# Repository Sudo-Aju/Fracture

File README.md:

<div align="center">

# 

A Bluetooth Powered 48-Key Split Keyboard

### _A keyboard designed to physically split apart - because productivity and aesthetics shouldn't stay connected._

</div>

---

# Overview

**Fracture** is a wireless 48-key split mechanical keyboard built around modularity, portability, and aesthetics.

Unlike traditional keyboards, Fracture is designed to **literally seperate into two halves**, giving users a more ergonomic typing expereience while creating a visually unique "fractured" appearance.

Built using the **Seed Studio XIAO nRF52840**, Kailh Choc Switches, and low-profile keycaps, Fracture blends minimalism with functionaly in a compact wireless setup.

---

# Gallery

<div align="center">

</div>

---

# Zine

<div align="center">

</div>

---

# Motivation

Most keyboards are designed around a fixed layout.

Fracture was built around a different idea:

> _What if keyboard itself reflected flexibility?_

The split design is inspired from Corne keyboards:
- Better ergonomics
- Adjustable positioning
- Cleaner desk setups
- Compact portability
- A visually striking design language

The project also explores how industrial design and hardware aesthetics can coexist with practicality.

---

# Assembly Guide

## Hardware

### 1. Order the PCB

Navigate to:

```bash
PCB/Production/
```

Upload the included Gerber files to your preferred PCB manufacturer and order the PCB.

### 2. Order the Components
All required components and purchase links are available inside: (India)
```bash
PCB/BOM/BOM.csv
```
Order all listed parts before starting assembly
### 3. Solder the SMD Components

Start by soldering first few SMD components on the PCB:
- Diodes are on the front
- MCU pads are on the back

It is recommended to use:
- Flux
- Dine-tip soldering iron
- Tweezers

### 4. Install Hot-Swap Sockets
- Solder all Kailh hot-swap sockets onto the PCB carefully.

- Ensure every socket sits completely flat agains the PCB before soldering.

### 5. Install the Rotary Encoders

- Solder the EC11 rotary encoders in their designated positions.

- Make sure they are aligned staright before fully soldering.

### 6. Insert the MCU

- Now the XIAO nRF52840 (or any other if changed) controllers onto the PCB. 

### 7. Assemble the Case

- Print the 3D enclosure, and inert the PCB by aligning its M3 screw holes with the joints.

### 8. Install Switches

- Insert all Kailh Choc switches into the plate and hot-swap sockets.

- Check alignment carefully to avoid bent pins.

### 9. Install Keycaps

- Press the keycaps firmly onto the switches,

## Firmware Installation

### 1. Enter Bootloader Mode
While the keyboard is unplugged:

- Short the `BOOT` and `GND` pads using tweezers or screwdriver
- Plug in the USB cable

or

- Double press the reset button on the XIAO nRF52840

A new drive should appear on your computer

### 2. Download Firmware

Naviagte to:
```bash
Firmware/
```
and download `adafruit-circuitpython-Seeed_XIAO_nRF52840_Sense-en_US-10.2.1.uf2` or compile the files in `Firmware/Config` file if ZMK is to be used.

### 3. Flash the Firmware

Drag and drop the `uf2` file onto the mounted drive.
Repeat for the second half as well.

---

# BOM

|Designator                                                                                                                                                                                                                                                                           |Function        |Value                               |Footprint                              |Quantity|Price (INR)|Price (USD)|Amount |Link                                                                                                                                                            |
|-------------------------------------------------------------------------------------------------------------------------------------------------------------------------------------------------------------------------------------------------------------------------------------|----------------|------------------------------------|---------------------------------------|--------|-----------|-----------|-------|----------------------------------------------------------------------------------------------------------------------------------------------------------------|
|PCB                                                                                                                                                                                                                                                                                  |Main PCB        |                                    |                                       |1       |₹3,969.00  |$40.71     |$40.71 |https://www.pcbpower.com/page/PCBDetails/UXVvdGF0aW9ucw==/SU5RNjAzNTY0/                                                                                         |
|Keycaps u1 1                                                                                                                                                                                                                                                                         |Slim Keycaps    |Chocfox CFX Choc Blank Keycaps u1   |SW_choc_v1_HS_CPG135001S30_1u          |40      |₹35.00     |$0.36      |$14.36 |https://neomacro.in/products/chocfox-cfx-choc-blank-keycaps                                                                                                     |
|Keycaps u1 2                                                                                                                                                                                                                                                                         |Slim Keycaps    |Chocfox CFX Choc Blank Keycaps u1   |SW_choc_v1_HS_CPG135001S30_1u          |4       |₹35.00     |$0.36      |$1.44  |https://neomacro.in/products/chocfox-cfx-choc-blank-keycaps?variant=48049351590166                                                                              |
|Keycaps u1.25                                                                                                                                                                                                                                                                        |Slim Keycaps    |Chocfox CFX Choc Blank Keycaps u1.25|SW_choc_v1_HS_CPG135001S30_1.25u       |2       |₹55.00     |$0.56      |$1.13  |https://neomacro.in/products/chocfox-cfx-choc-blank-keycaps?variant=48049351622934                                                                              |
|Keycaps u1.5                                                                                                                                                                                                                                                                         |Slim Keycaps    |Chocfox CFX Choc Blank Keycaps u1.5 |SW_choc_v1_HS_CPG135001S30_1.5u        |2       |₹55.00     |$0.56      |$1.13  |https://neomacro.in/products/chocfox-cfx-choc-blank-keycaps?variant=48049351655702                                                                              |
|Enclosure                                                                                                                                                                                                                                                                            |Print Legion    |                                    |                                       |1       |₹400.00    |$4.10      |$4.10  |https://printlegion.hackclub.com/                                                                                                                               |
|D35, D36, D37, D38, D39, D40, D41, D42, D43, D44, D45, D46, D47, D48, D49, D50, D51, D52, D53, D54, D55, D56, D57, D58, D59, D60, D61, D62, D63, D64, D65, D66, D67, D68, D69, D70, D71, D72, D73, D74, D75, D76, D77, D78, D80, D81, D82, D83                                       |Diodes          |1N4148W                             |D_SOD-123                              |48      |₹0.70      |$0.01      |$0.34  |https://robu.in/product/1n4148w-sod-123-1206-diodereel-of-3000/                                                                                                 |
|SW1, SW2, SW3, SW4, SW5, SW6, SW7, SW8, SW9, SW10, SW11, SW12, SW13, SW14, SW15, SW16, SW17, SW18, SW19, SW20, SW21, SW22, SW23, SW24, SW26, SW29, SW30, SW31, SW33, SW34, SW36, SW37, SW38, SW39, SW40, SW41, SW42, SW43, SW44, SW45, SW46, SW47, SW48, SW49, SW25, SW32, SW27, SW28|Keys            |Kailh Choc u1                       |SW_choc_v1_HS_CPG135001S30             |44      |₹54.55     |$0.56      |$24.62 |https://neomacro.in/products/kailh-choc-v1-switches                                                                                                             |
|SW35, SW50                                                                                                                                                                                                                                                                           |Rotary Encoders |EC11                                |RotaryEncoder_Alps_EC11E_Vertical_H20mm|2       |₹42.00     |$0.43      |$0.86  |https://www.flyrobo.in/ec11-rotary-encoder-half-shaft-handle-potentiometer-15mm?tracking=ads&srsltid=AfmBOorjqwhfobDZ2HP5h3FZMTYz27RTBOT3YmNnFShFGbmHEdoPsKBgEZg|
|U1, U2                                                                                                                                                                                                                                                                               |MCU             |XIAO nRF52840                       |modified-XIAO-nRF52840-SMD             |2       |₹1,152.00  |$11.82     |$23.63 |https://robu.in/product/seeed-studio-xiao-ble-nrf52840/                                                                                                         |
|SW1, SW2, SW3, SW4, SW5, SW6, SW7, SW8, SW9, SW10, SW11, SW12, SW13, SW14, SW15, SW16, SW17, SW18, SW19, SW20, SW21, SW22, SW23, SW24, SW26, SW29, SW30, SW31, SW33, SW34, SW36, SW37, SW38, SW39, SW40, SW41, SW42, SW43, SW44, SW45, SW46, SW47, SW48, SW49                        |Hot-swap Sockets|Kailh HS choc v1                    |SW_choc_v1_HS_CPG135001S30             |48      |₹14.00     |$0.14      |$6.89  |https://neomacro.in/products/kailh-choc-pg1350-hot-swap-sockets?variant=48049369907478                                                                          |
|TOTAL                                                                                                                                                                                                                                                                                |                |                                    |                                       |        |           |           |$119.21|                                                                                                                                                                |
---

# Features

- **Physically Splits Into Two Halves**
- **Bluetooth Powered**
- **48-Key Layout**
- **Rotary Encoders**
- **Low Profile Kailh Choc Switches**
- **Kailh Hot-Swap Sockets**
- **Powered by XIAO nRF52840**
- **Custom Themed Enclosure**
- **Slim Keycaps**
- **Portable & Lightweigth**
- **Fully Custom PCB**

___

# Hardware Stack

| Component | Description |
|---|---|
| MCU | Seeed Studio XIAO nRF52840 |
| Switches | Kailh Choc Low Profile |
| Sockets | Kailh Hot Swap Sockets |
| Layout | 48-key Split |
| Connectivity | Bluetooth |
| Encoders | Rotary Encoders (360 Degree Rotary Encoder EC16)
| Keycaps | Slim Low-Profile Keycaps |
| PCB | Custom Designes |
| Case | Themed Fracture Enclosure |

---

# PCB Design

The PCB was custom designed specifically for the Fracture layout and enclosure.

Features include:
- Wireless microcontroller support
- Rotary encoder integration
- Kailh hot-swap compatibility
- Compact routing for slip profile construction

## PCB

## Schematic

## Placement

---

# Enclosure

The enclosure follows the central "fracture" design language:
- Broken center seam
- Aggresive angular styling
- Compact low-profile body
- Seamless split mechanism

The goal was to make the keyboard feel more like a designed object rather than just a perpheral.

---

# Firmware (ZMK)

Firmware features:
- Bluetooth support
- Custom keymaps
- Layer switching
- Encoder controls

---

```bash
Fracture/
├── PCB/
├── CAD/
├── Firmware/
├── Assets/
└── README.md
```

---

# Current Status

- [X] Inital Concept
- [X] Layout Finalized
- [X] Enclosure Prototype
- [X] PCB design
- [X] Firmware
- [ ] Final Build
- [ ] Firmware Optimization

---

# Contributing 

Contributions, suggestions, and feedback are welcome.

If you'd like to improve Fracture:
1. Fork or Clone the repository 
```bash
git clone https://github.com/Sudo-Aju/Fracture.git
cd Fracture
```
2. Create your feature branch (if forked)
3. Commit your changes
4. Open a pull request

---

# Creator

### Azmeer Pirani
17 • India • @fallout

Built with a love for:
- hardware design
- industrial aesthetics
- mechanical keyboards
- expirimental products

---

# License

This project is licensed under the MIT License.

---

<div align="center">

## FRACTURE

### _Break the keyboard. Not the workflow._

</div>

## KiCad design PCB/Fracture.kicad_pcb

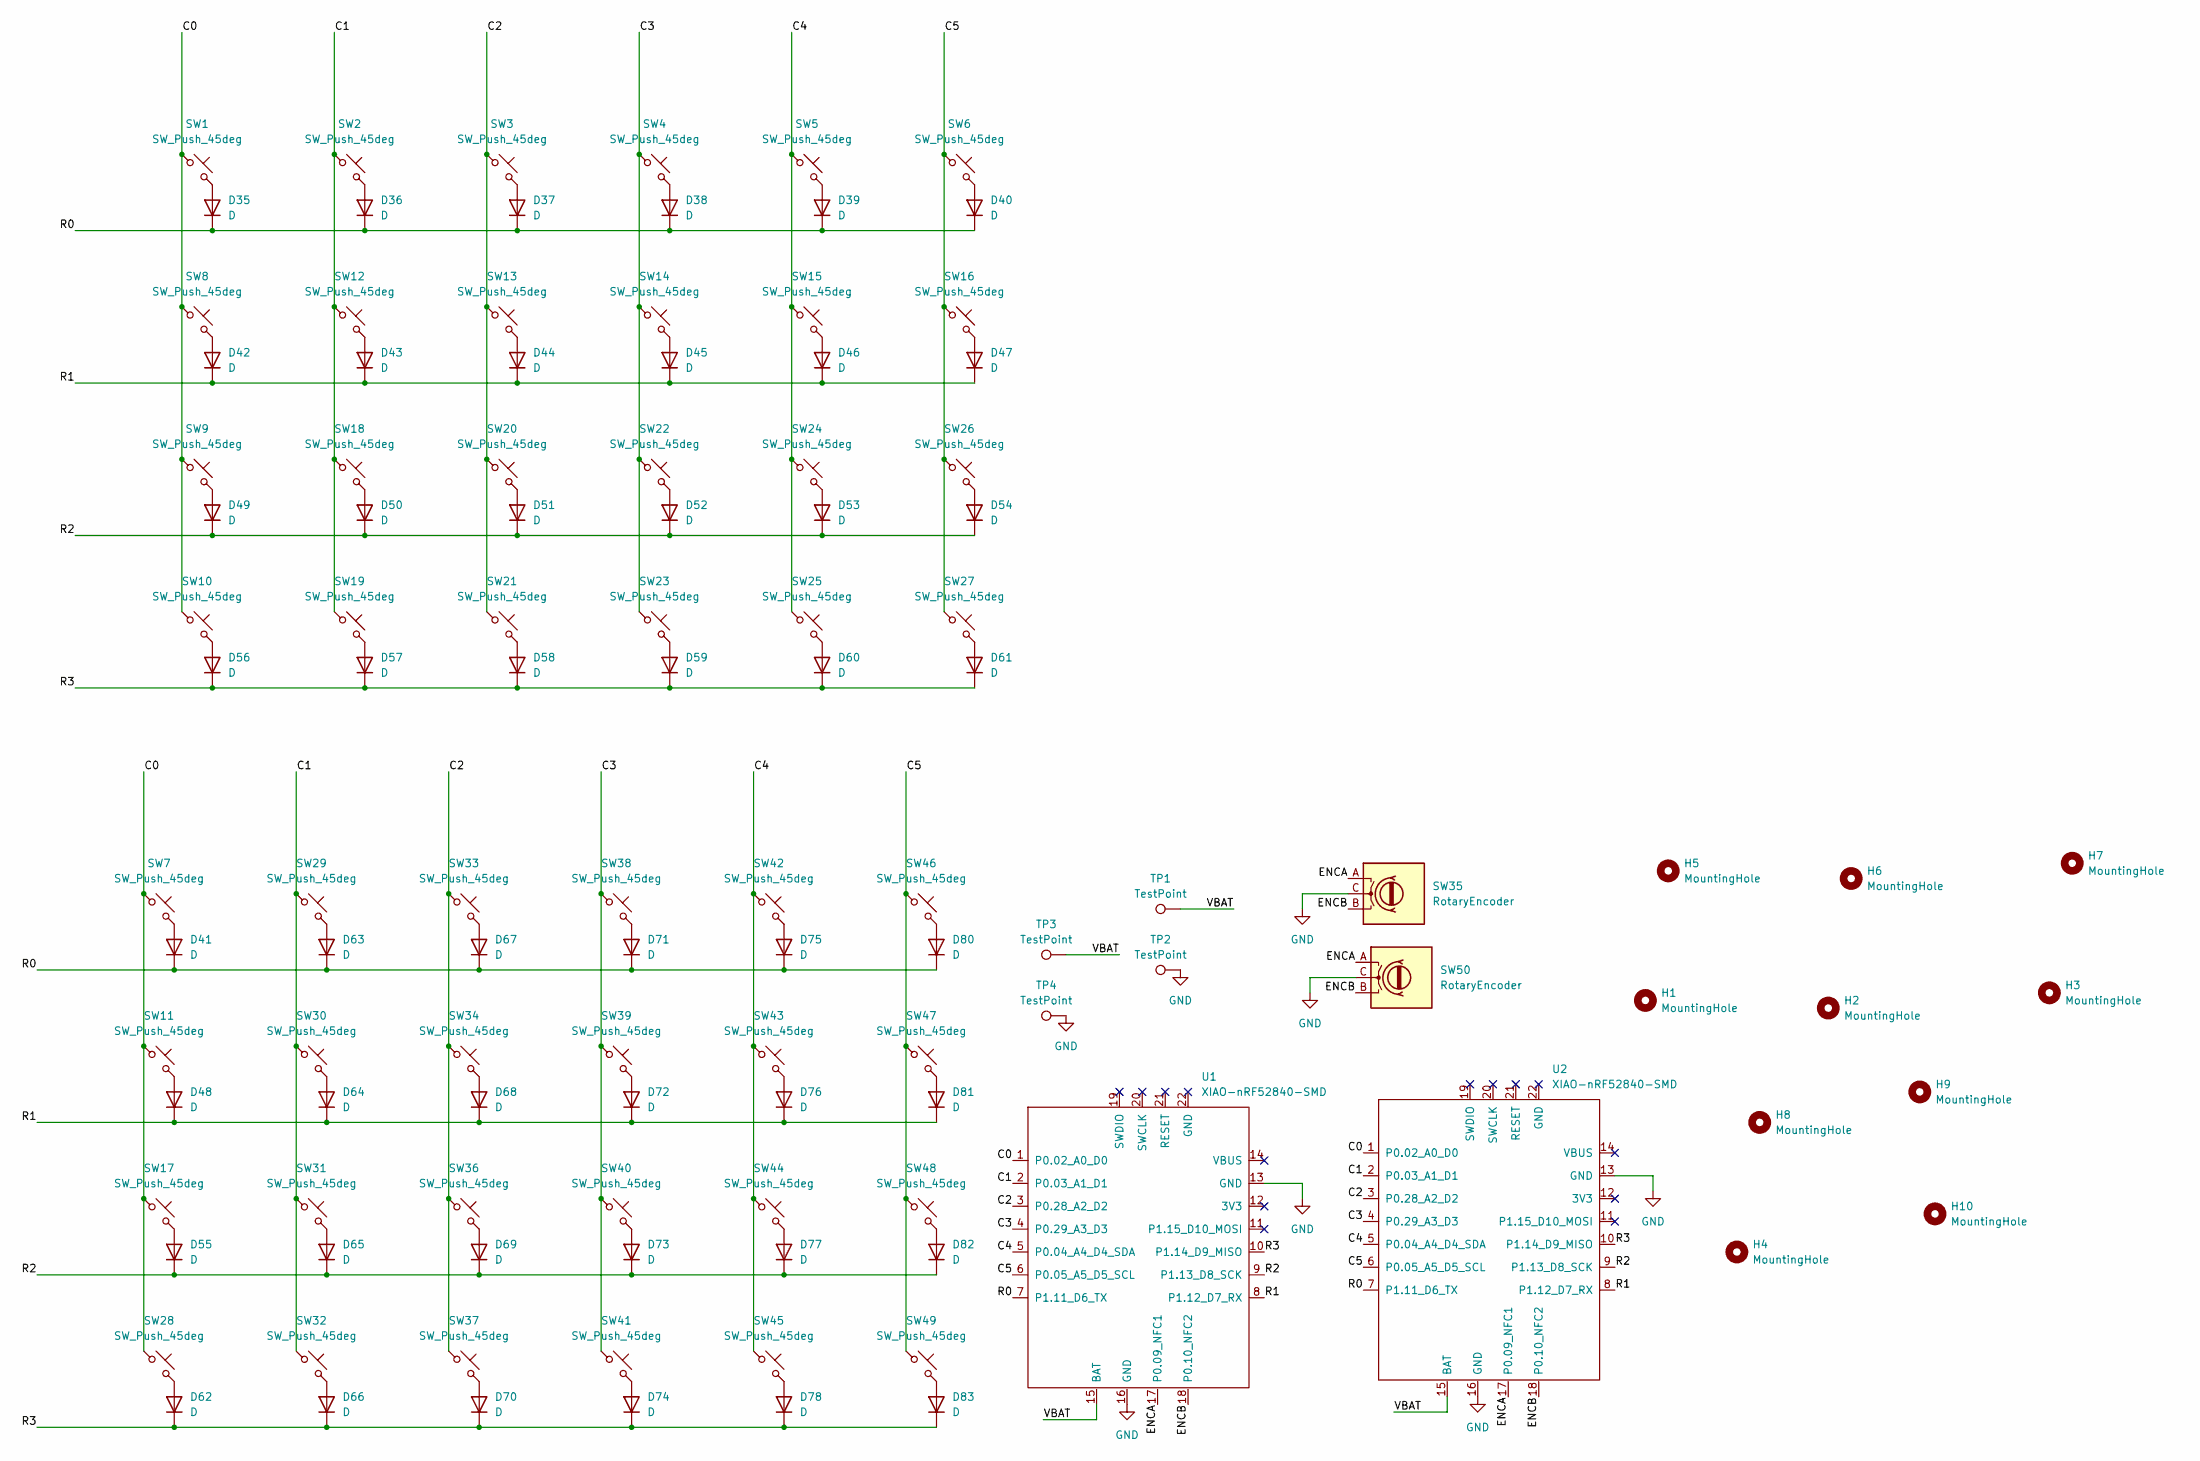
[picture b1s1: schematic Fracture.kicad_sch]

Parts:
D35, D36, D37, D38, D39, D40, D41, D42, D43, D44, D45, D46, D47, D48, D49, D50, D51, D52, D53, D54, D55, D56, D57, D58, D59, D60, D61, D62, D63, D64, D65, D66, D67, D68, D69, D70, D71, D72, D73, D74, D75, D76, D77, D78, D80, D81, D82, D83: D; D_SOD-123
H1, H2, H3, H4, H5, H6, H7, H8: MountingHole; MountingHole_3mm
H9, H10: MountingHole; MouseBite-Slot_2.0x2.0mm_outset_D0.5mm_P0.85mm_3h
SW1, SW2, SW3, SW4, SW5, SW6, SW7, SW8, SW9, SW10, SW11, SW12, SW13, SW14, SW15, SW16, SW17, SW18, SW19, SW20, SW21, SW22, SW23, SW24, SW25, SW26, SW27, SW28, SW29, SW30, SW31, SW32, SW33, SW34, SW36, SW37, SW38, SW39, SW40, SW41, SW42, SW43, SW44, SW45, SW46, SW47, SW48, SW49: SW_Push_45deg; SW_choc_v1_HS_CPG135001S30_1u
SW35, SW50: RotaryEncoder; RotaryEncoder_Alps_EC11E_Vertical_H20mm
TP1, TP2, TP3, TP4: TestPoint; TestPoint_Pad_D2.0mm
U1, U2: XIAO-nRF52840-SMD; modified-XIAO-nRF52840-SMD

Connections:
/C0: SW1.1, SW7.1, SW8.1, SW9.1, SW10.1, SW11.1, SW17.1, SW28.1, U1.1 (P0.02_A0_D0), U2.1 (P0.02_A0_D0)
/C1: SW2.1, SW12.1, SW18.1, SW19.1, SW29.1, SW30.1, SW31.1, SW32.1, U1.2 (P0.03_A1_D1), U2.2 (P0.03_A1_D1)
/C2: SW3.1, SW13.1, SW20.1, SW21.1, SW33.1, SW34.1, SW36.1, SW37.1, U1.3 (P0.28_A2_D2), U2.3 (P0.28_A2_D2)
/C3: SW4.1, SW14.1, SW22.1, SW23.1, SW38.1, SW39.1, SW40.1, SW41.1, U1.4 (P0.29_A3_D3), U2.4 (P0.29_A3_D3)
/C4: SW5.1, SW15.1, SW24.1, SW25.1, SW42.1, SW43.1, SW44.1, SW45.1, U1.5 (P0.04_A4_D4_SDA), U2.5 (P0.04_A4_D4_SDA)
/C5: SW6.1, SW16.1, SW26.1, SW27.1, SW46.1, SW47.1, SW48.1, SW49.1, U1.6 (P0.05_A5_D5_SCL), U2.6 (P0.05_A5_D5_SCL)
/ENCA: SW35.A, SW50.A, U1.17 (P0.09_NFC1), U2.17 (P0.09_NFC1)
/ENCB: SW35.B, SW50.B, U1.18 (P0.10_NFC2), U2.18 (P0.10_NFC2)
/R0: D35.1 (K), D36.1 (K), D37.1 (K), D38.1 (K), D39.1 (K), D40.1 (K), D41.1 (K), D63.1 (K), D67.1 (K), D71.1 (K), D75.1 (K), D80.1 (K), U1.7 (P1.11_D6_TX), U2.7 (P1.11_D6_TX)
/R1: D42.1 (K), D43.1 (K), D44.1 (K), D45.1 (K), D46.1 (K), D47.1 (K), D48.1 (K), D64.1 (K), D68.1 (K), D72.1 (K), D76.1 (K), D81.1 (K), U1.8 (P1.12_D7_RX), U2.8 (P1.12_D7_RX)
/R2: D49.1 (K), D50.1 (K), D51.1 (K), D52.1 (K), D53.1 (K), D54.1 (K), D55.1 (K), D65.1 (K), D69.1 (K), D73.1 (K), D77.1 (K), D82.1 (K), U1.9 (P1.13_D8_SCK), U2.9 (P1.13_D8_SCK)
/R3: D56.1 (K), D57.1 (K), D58.1 (K), D59.1 (K), D60.1 (K), D61.1 (K), D62.1 (K), D66.1 (K), D70.1 (K), D74.1 (K), D78.1 (K), D83.1 (K), U1.10 (P1.14_D9_MISO), U2.10 (P1.14_D9_MISO)
/VBAT: TP1.1 (1_1), TP3.1 (1_1), U1.15 (BAT), U2.15 (BAT)
GND: SW35.C, SW50.C, TP2.1 (1_1), TP4.1 (1_1), U1.13 (GND), U1.16 (GND), U2.13 (GND), U2.16 (GND)
unnamed: D35.2 (A), SW1.2
unnamed: D36.2 (A), SW2.2
unnamed: D37.2 (A), SW3.2
unnamed: D38.2 (A), SW4.2
unnamed: D39.2 (A), SW5.2
unnamed: D40.2 (A), SW6.2
unnamed: D41.2 (A), SW7.2
unnamed: D42.2 (A), SW8.2
unnamed: D43.2 (A), SW12.2
unnamed: D44.2 (A), SW13.2
unnamed: D45.2 (A), SW14.2
unnamed: D46.2 (A), SW15.2
unnamed: D47.2 (A), SW16.2
unnamed: D48.2 (A), SW11.2
unnamed: D49.2 (A), SW9.2
unnamed: D50.2 (A), SW18.2
unnamed: D51.2 (A), SW20.2
unnamed: D52.2 (A), SW22.2
unnamed: D53.2 (A), SW24.2
unnamed: D54.2 (A), SW26.2
unnamed: D55.2 (A), SW17.2
unnamed: D56.2 (A), SW10.2
unnamed: D57.2 (A), SW19.2
unnamed: D58.2 (A), SW21.2
unnamed: D59.2 (A), SW23.2
unnamed: D60.2 (A), SW25.2
unnamed: D61.2 (A), SW27.2
unnamed: D62.2 (A), SW28.2
unnamed: D63.2 (A), SW29.2
unnamed: D64.2 (A), SW30.2
unnamed: D65.2 (A), SW31.2
unnamed: D66.2 (A), SW32.2
unnamed: D67.2 (A), SW33.2
unnamed: D68.2 (A), SW34.2
unnamed: D69.2 (A), SW36.2
unnamed: D70.2 (A), SW37.2
unnamed: D71.2 (A), SW38.2
unnamed: D72.2 (A), SW39.2
unnamed: D73.2 (A), SW40.2
unnamed: D74.2 (A), SW41.2
unnamed: D75.2 (A), SW42.2
unnamed: D76.2 (A), SW43.2
unnamed: D77.2 (A), SW44.2
unnamed: D78.2 (A), SW45.2
unnamed: D80.2 (A), SW46.2
unnamed: D81.2 (A), SW47.2
unnamed: D82.2 (A), SW48.2
unnamed: D83.2 (A), SW49.2

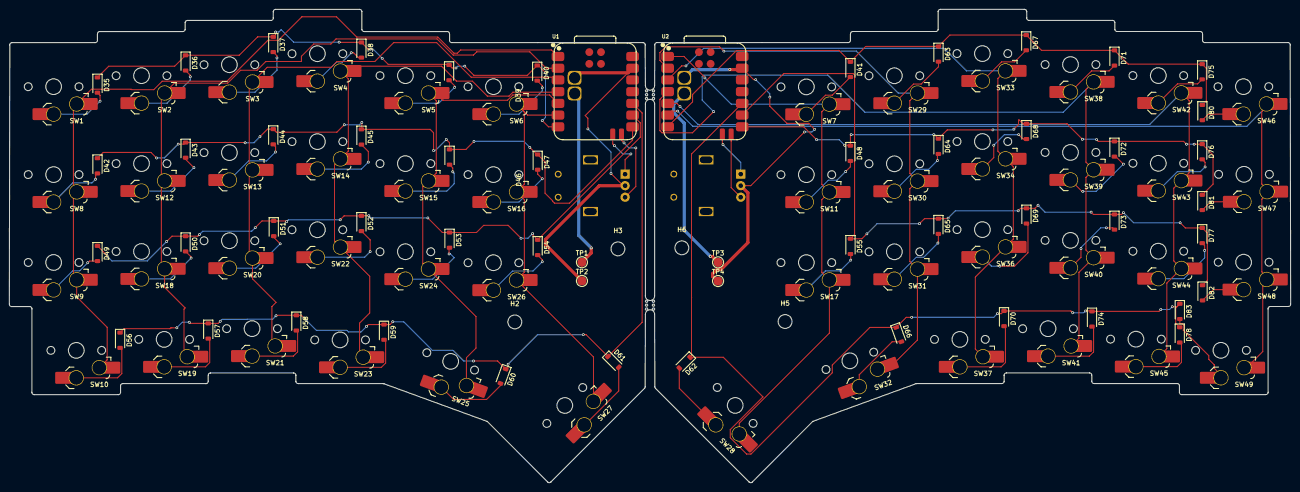
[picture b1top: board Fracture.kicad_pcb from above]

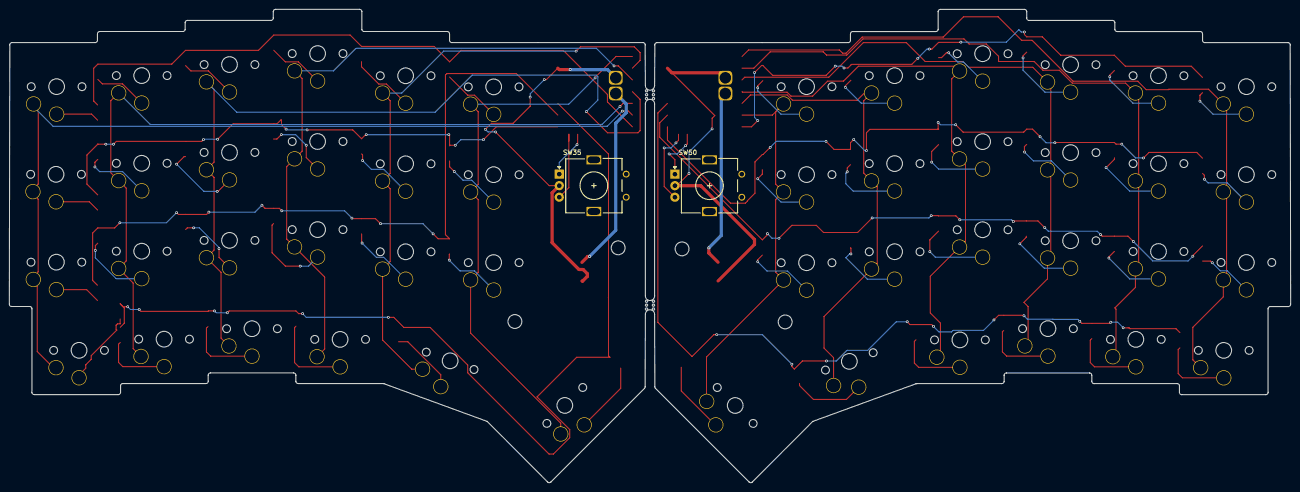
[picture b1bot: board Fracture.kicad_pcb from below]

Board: 2 copper layers, 277.7 x 102.6 mm, 110 parts (2 on the bottom side), 62 nets.

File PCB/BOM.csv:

"Id";"Designator";"Footprint";"Quantity";"Designation";"Supplier and ref";
1;"D35, D36, D37, D38, D39, D40, D41, D42, D43, D44, D45, D46, D47, D48, D49, D50, D51, D52, D53, D54, D55, D56, D57, D58, D59, D60, D61, D62, D63, D64, D65, D66, D67, D68, D69, D70, D71, D72, D73, D74, D75, D76, D77, D78, D80, D81, D82, D83";"D_SOD-123";48;"D";;;
2;"SW1, SW2, SW3, SW4, SW5, SW6, SW7, SW8, SW9, SW10, SW11, SW12, SW13, SW14, SW15, SW16, SW17, SW18, SW19, SW20, SW21, SW22, SW23, SW24, SW26, SW29, SW30, SW31, SW33, SW34, SW36, SW37, SW38, SW39, SW40, SW41, SW42, SW43, SW44, SW45, SW46, SW47, SW48, SW49";"SW_choc_v1_HS_CPG135001S30_1u";44;"SW_Push_45deg";;;
3;"SW25, SW32";"SW_choc_v1_HS_CPG135001S30_1.25u";2;"SW_Push_45deg";;;
4;"SW27, SW28";"SW_choc_v1_HS_CPG135001S30_1.5u";2;"SW_Push_45deg";;;
5;"SW35, SW50";"RotaryEncoder_Alps_EC11E_Vertical_H20mm";2;"RotaryEncoder";;;
6;"TP1, TP2, TP3, TP4";"TestPoint_Pad_D2.0mm";4;"TestPoint";;;
7;"U1, U2";"modified-XIAO-nRF52840-SMD";2;"XIAO-nRF52840-SMD";;;

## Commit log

2026-05-23 first commit, i have now added all the files + the zine page
2026-05-24 updated readme and added assets like logo
2026-05-24 updated logo
2026-05-24 Added few more stuff in readme, added a preveiw and features section
2026-05-24 revision
2026-05-24 added hardware stack section
2026-05-24 added PCB desing and philoisy seciotn
2026-05-24 added new sections
2026-05-24 added gallery and updated images
2026-05-24 updated images
2026-05-24 updated reamde
2026-05-24 added bom
2026-05-24 Remove .DS_Store files from tracking
2026-05-24 done with the firmware
2026-05-24 updated the readme
2026-05-24 updated the image
2026-05-24 updated the files
2026-05-25 updated readme, added steps to assemble and make the keyboard
2026-05-25 added libraires
2026-05-25 added individual cad files for components
2026-05-25 updated readme, added more instructions
